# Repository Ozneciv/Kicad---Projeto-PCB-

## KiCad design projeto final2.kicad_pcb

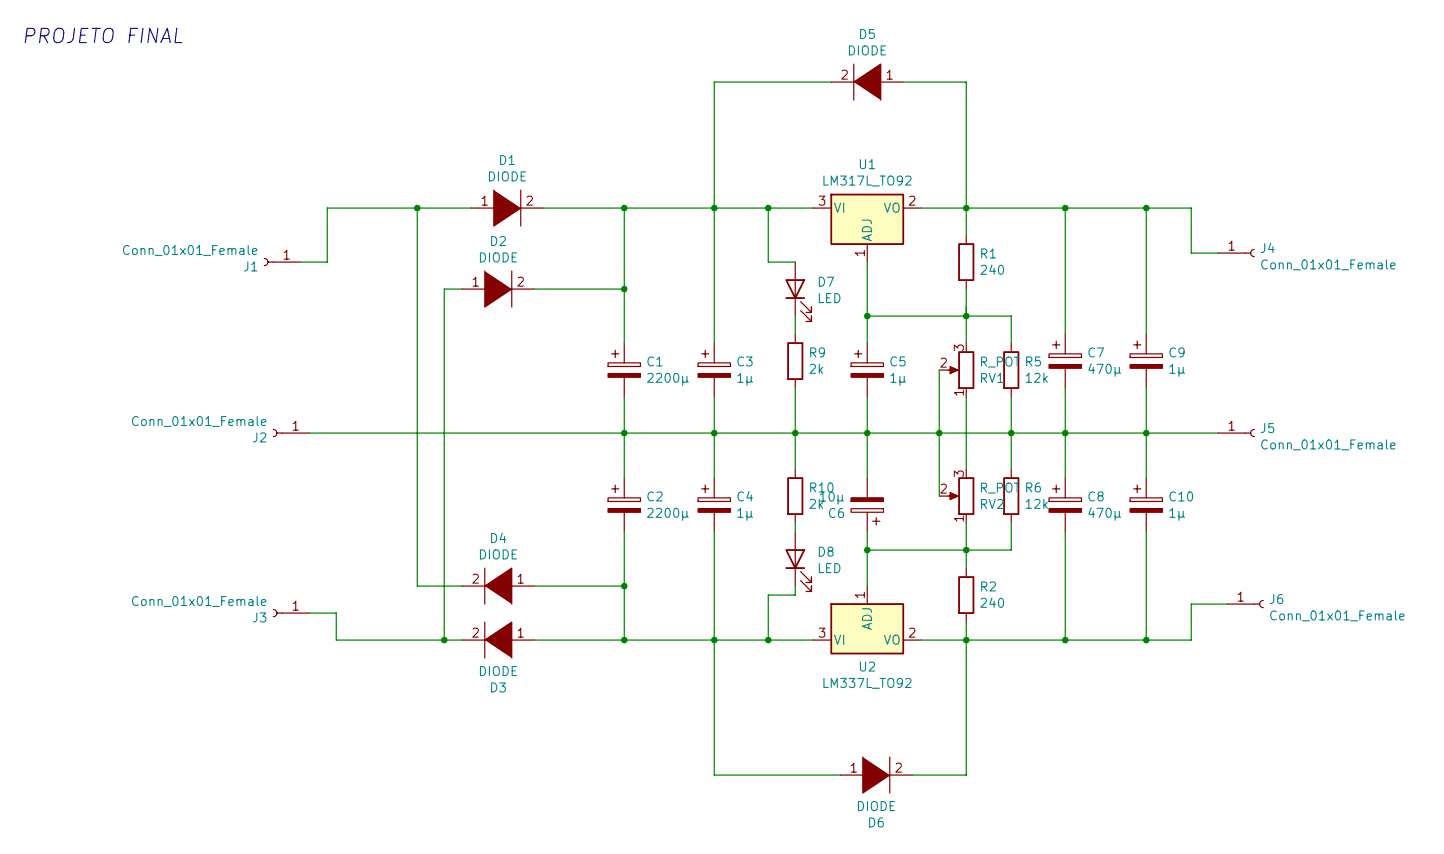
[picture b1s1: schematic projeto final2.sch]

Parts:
C1, C2: 2200μ; CP_Radial_D12.5mm_P5.00mm
C3, C4, C5, C9, C10: 1μ; CP_Radial_D5.0mm_P2.00mm
C6: 10μ; CP_Radial_D5.0mm_P2.00mm
C7, C8: 470μ; CP_Radial_D10.0mm_P2.50mm
D1, D2, D3, D4, D5, D6: DIODE; D_DO-41_SOD81_P10.16mm_Horizontal
D7, D8: LED; LED_D5.0mm
J1, J2, J3, J4, J5, J6: Conn_01x01_Female; Banana_Jack_1Pin
R1, R2: 240; R_Axial_DIN0204_L3.6mm_D1.6mm_P7.62mm_Horizontal
R5, R6: 12k; R_Axial_DIN0204_L3.6mm_D1.6mm_P7.62mm_Horizontal
R9, R10: 2k; R_Axial_DIN0204_L3.6mm_D1.6mm_P7.62mm_Horizontal
RV1, RV2: R_POT; Potentiometer_Alps_RK163_Single_Horizontal
U1: LM317L_TO92; TO-220-3_Vertical
U2: LM337L_TO92; TO-220-3_Vertical

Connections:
GND: C1.2, C2.1, C3.2, C4.1, C5.2, C6.2, C7.2, C8.1, C9.2, C10.1, J2.1, J5.1, R5.2, R6.1, R9.2, R10.1, RV1.2, RV2.2
unnamed: C1.1, C3.1, D1.2 (A), D2.2 (A), D5.2 (A), D7.2 (A), U1.3 (VI)
unnamed: C2.2, C4.2, D3.1 (K), D4.1 (K), D6.1 (K), D8.1 (K), U2.3 (VI)
unnamed: C5.1, R1.2, R5.1, RV1.3, U1.1 (ADJ)
unnamed: C6.1, R2.1, R6.2, RV2.1, U2.1 (ADJ)
unnamed: C7.1, C9.1, D5.1 (K), J4.1, R1.1, U1.2 (VO)
unnamed: C8.2, C10.2, D6.2 (A), J6.1, R2.2, U2.2 (VO)
unnamed: D1.1 (K), D4.2 (A), J1.1
unnamed: D2.1 (K), D3.2 (A), J3.1
unnamed: D7.1 (K), R9.1
unnamed: D8.2 (A), R10.2
unnamed: RV1.1, RV2.3

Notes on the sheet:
PROJETO FINAL

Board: 2 copper layers, 34 parts (0 on the bottom side), 12 nets, no tracks yet.
